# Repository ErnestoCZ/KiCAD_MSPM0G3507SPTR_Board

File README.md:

# MSPM0G3507 Board

Ein KiCad-Projekt: kompaktes Entwicklungsboard rund um den **TI MSPM0G3507SPTR**.

<!-- TODO: Foto oder 3D-Render des Boards einfügen -->
<!--  -->

## ✨ Features

- **MCU:** MSPM0G3507SPTR – Arm Cortex-M0+ mit bis zu 80 MHz, 128 KB Flash, 32 KB SRAM
- **Peripherie des Chips:** CAN-FD, 12-Bit-ADC, DAC, Op-Amp, UART, SPI, I²C
- TODO: Stromversorgung (z. B. USB-C, 3,3-V-Regler)
- TODO: Programmierung/Debugging (z. B. SWD-Header)
- TODO: Herausgeführte Pins, LEDs, Taster, Sensoren

## 📁 Projektstruktur

```text
.
├── *.kicad_pro      # KiCad-Projekt
├── *.kicad_sch      # Schaltplan
├── *.kicad_pcb      # Platinenlayout
├── libs/            # Symbole & Footprints (falls vorhanden)
└── README.md
```

## 🚀 Loslegen

1. Repository klonen:
   ```bash
   git clone https://github.com/ErnestoCZ/KiCAD_MSPM0G3507SPTR_Board.git
   ```
2. Projektdatei `*.kicad_pro` in [KiCad](https://www.kicad.org/) öffnen (TODO: Version angeben, z. B. 8.x).
3. Schaltplan und Layout ansehen, bei Bedarf Gerber-Dateien exportieren.

## 🔧 Firmware

Der MSPM0G3507 wird mit dem [TI MSPM0 SDK](https://www.ti.com/tool/MSPM0-SDK) und Code Composer Studio (oder einer Toolchain deiner Wahl) programmiert.

## 📌 Status

TODO: z. B. „Prototyp in Arbeit“ / „Rev. A bestellt“ / „getestet“

## 📄 Lizenz

TODO: Lizenz wählen (z. B. CERN-OHL-P für Hardware, MIT für Code)

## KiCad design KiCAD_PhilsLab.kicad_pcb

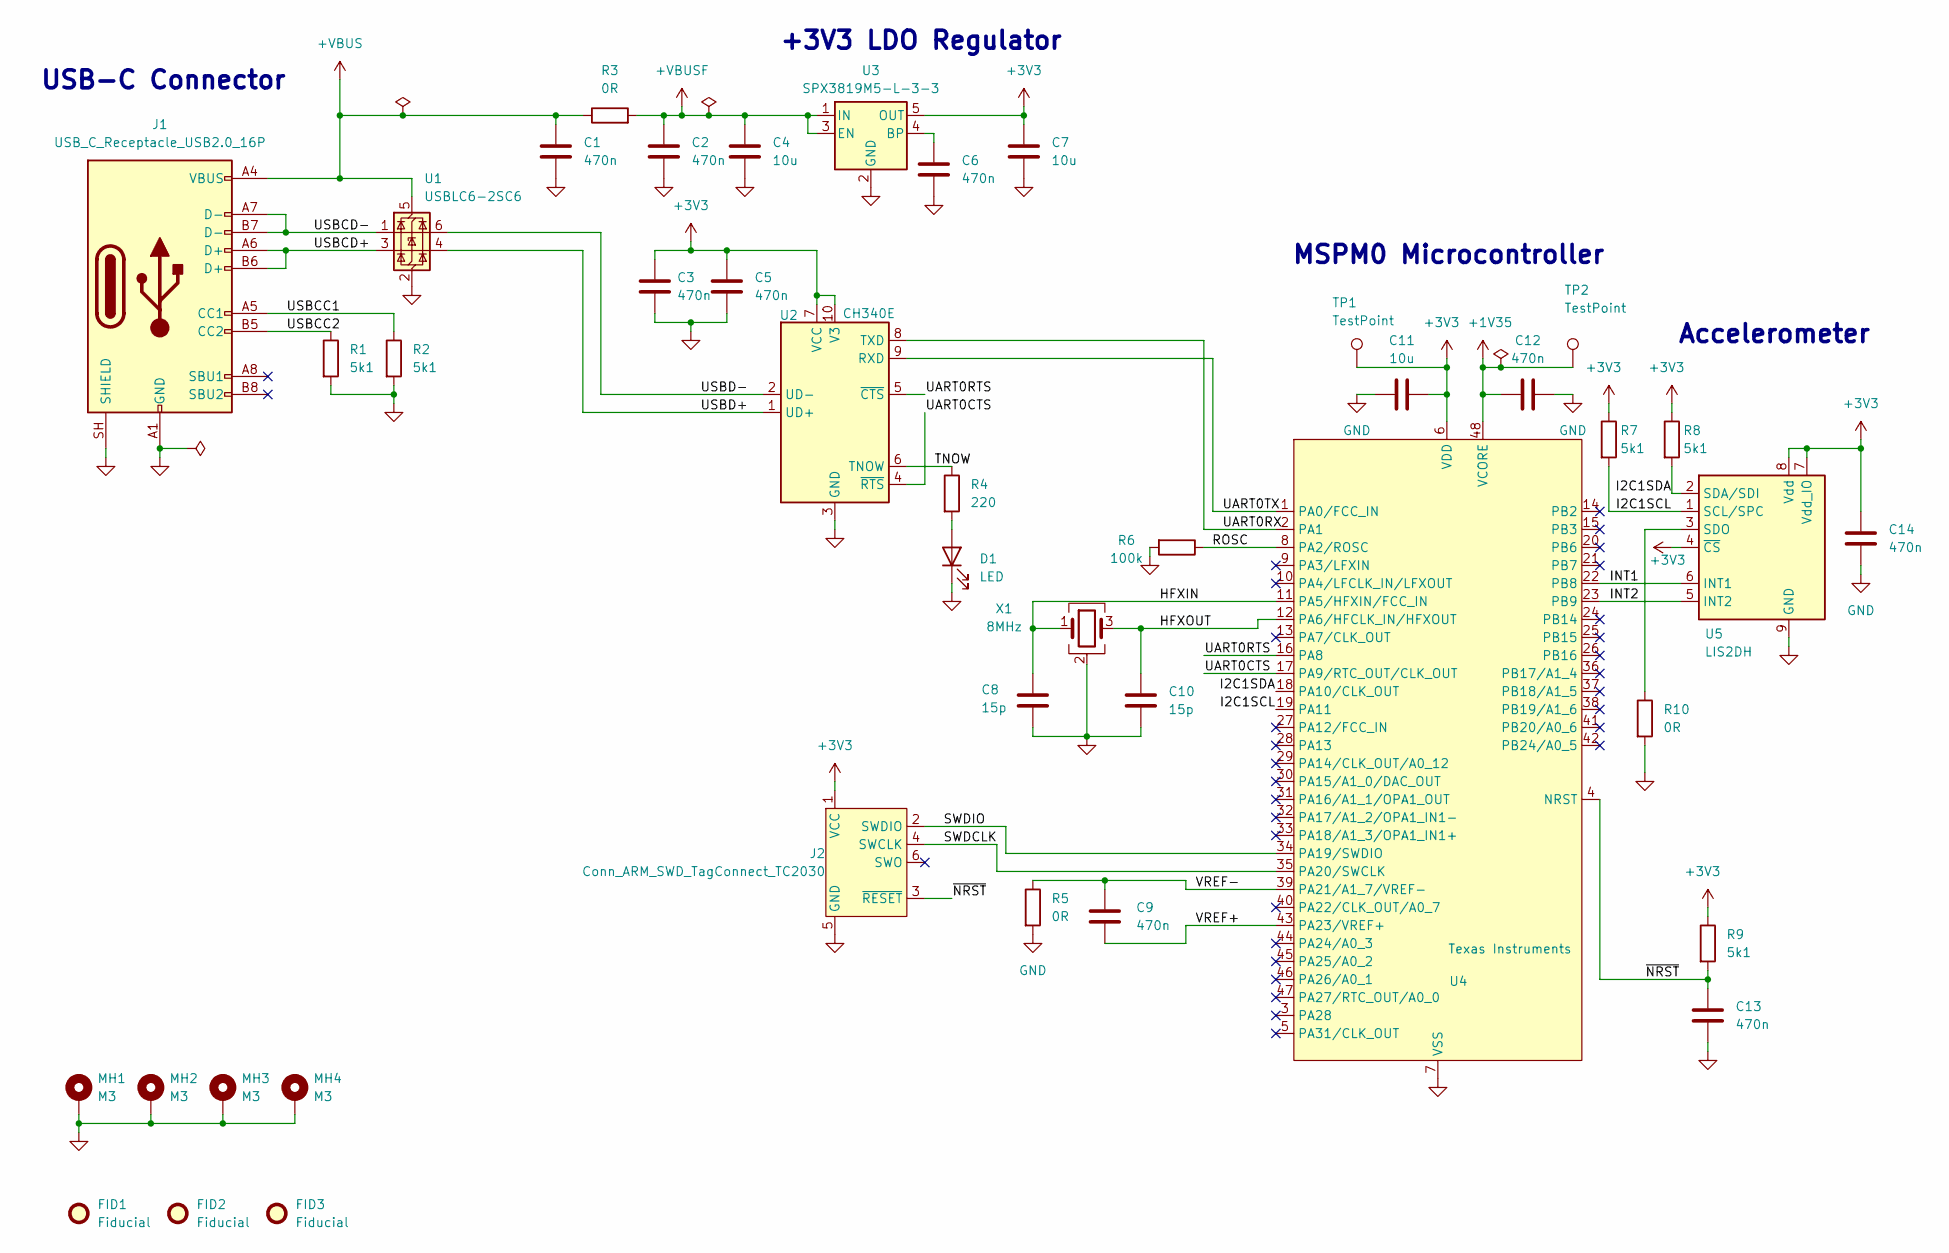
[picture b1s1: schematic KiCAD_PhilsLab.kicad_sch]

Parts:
C1, C2, C3, C5, C6, C9, C12, C13, C14: 470n; C_0603_1608Metric
C4, C7, C11: 10u; C_0805_2012Metric
C8, C10: 15p; C_0603_1608Metric
D1: LED; LED_0603_1608Metric
FID1, FID2, FID3: Fiducial; Fiducial_1mm_Mask2mm
J1: USB_C_Receptacle_USB2.0_16P; USB_C_Receptacle_GCT_USB4105-xx-A_16P_TopMnt_Horizontal
J2: Conn_ARM_SWD_TagConnect_TC2030; Tag-Connect_TC2030-IDC-FP_2x03_P1.27mm_Vertical
MH1, MH2, MH3, MH4: M3; MountingHole_3.2mm_M3_Pad_Via
R1, R2, R7, R8, R9: 5k1; R_0603_1608Metric
R3, R5, R10: 0R; R_0603_1608Metric
R4: 220; R_0201_0603Metric
R6: 100k; R_0603_1608Metric
TP1, TP2: TestPoint; TestPoint_Pad_D1.0mm
U1: USBLC6-2SC6; SOT-23-6
U2: CH340E; MSOP-10_3x3mm_P0.5mm
U3: SPX3819M5-L-3-3; SOT-23-5
U4: LQFP-48_7x7mm_P0.5mm
U5: LIS2DH; LGA-14_2x2mm_P0.35mm_LayoutBorder3x4y
X1: 8MHz; Crystal_SMD_3225-4Pin_3.2x2.5mm_HandSoldering

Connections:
+1V35: C12.1, TP2.1 (1_1), U4.48 (VCORE)
+3V3: C3.2, C5.2, C7.2, C11.2, C14.2, J2.1 (VCC), R7.1, R8.1, R9.1, TP1.1 (1_1), U2.7 (VCC), U2.10 (V3), U3.5 (OUT), U4.6 (VDD), U5.4 (~CS), U5.7 (Vdd_IO), U5.8 (Vdd)
+VBUS: C1.2, J1.A4 (VBUS), J1.A9 (VBUS), J1.B4 (VBUS), J1.B9 (VBUS), R3.1, U1.5 (VBUS)
+VBUSF: C2.2, C4.2, R3.2, U3.1 (IN), U3.3 (EN)
/HFXIN: C8.2, U4.11 (PA5/HFXIN/FCC_IN), X1.1
/HFXOUT: C10.1, U4.12 (PA6/HFCLK_IN/HFXOUT), X1.3
/I2C1SCL: R7.2, U4.19 (PA11), U5.1 (SCL/SPC)
/I2C1SDA: R8.2, U4.18 (PA10/CLK_OUT), U5.2 (SDA/SDI)
/INT1: U4.22 (PB8), U5.6 (INT1)
/INT2: U4.23 (PB9), U5.5 (INT2)
/ROSC: R6.1, U4.8 (PA2/ROSC)
/SWDCLK: J2.4 (SWCLK), U4.35 (PA20/SWCLK)
/SWDIO: J2.2 (SWDIO), U4.34 (PA19/SWDIO)
/TNOW: R4.1, U2.6 (TNOW)
/UART0CTS: U2.4 (~RTS), U4.17 (PA9/RTC_OUT/CLK_OUT)
/UART0RTS: U2.5 (~CTS), U4.16 (PA8)
/UART0RX: U2.8 (TXD), U4.2 (PA1)
/UART0TX: U2.9 (RXD), U4.1 (PA0/FCC_IN)
/USBCC1: J1.A5 (CC1), R2.1
/USBCC2: J1.B5 (CC2), R1.1
/USBCD+: J1.A6 (D+), J1.B6 (D+), U1.3 (I/O2)
/USBCD-: J1.A7 (D-), J1.B7 (D-), U1.1 (I/O1)
/USBD+: U1.4 (I/O2), U2.1 (UD+)
/USBD-: U1.6 (I/O1), U2.2 (UD-)
/VREF+: C9.2, U4.43 (PA23/VREF+)
/VREF-: C9.1, R5.1, U4.39 (PA21/A1_7/VREF-)
/~NRST: C13.1, J2.3 (~RESET), R9.2, U4.4 (NRST)
GND: C1.1, C2.1, C3.1, C4.1, C5.1, C6.1, C7.1, C8.1, C10.2, C11.1, C12.2, C13.2, C14.1, D1.1 (K), J1.A1 (GND), J1.A12 (GND), J1.B1 (GND), J1.B12 (GND), J1.SH (SHIELD), J2.5 (GND), MH1.1 (1_1), MH2.1 (1_1), MH3.1 (1_1), MH4.1 (1_1), R1.2, R2.2, R5.2, R6.2, R10.2, U1.2 (GND), U2.3 (GND), U3.2 (GND), U4.7 (VSS), U5.9 (GND), U5.11 (GND), X1.2 (G), X1.4 (G)
unnamed: D1.2 (A), R4.2
unnamed: C6.2, U3.4 (BP)
unnamed: R10.1, U5.3 (SDO)

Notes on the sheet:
MSPM0 Microcontroller
+3V3 LDO Regulator
Accelerometer
USB-C Connector

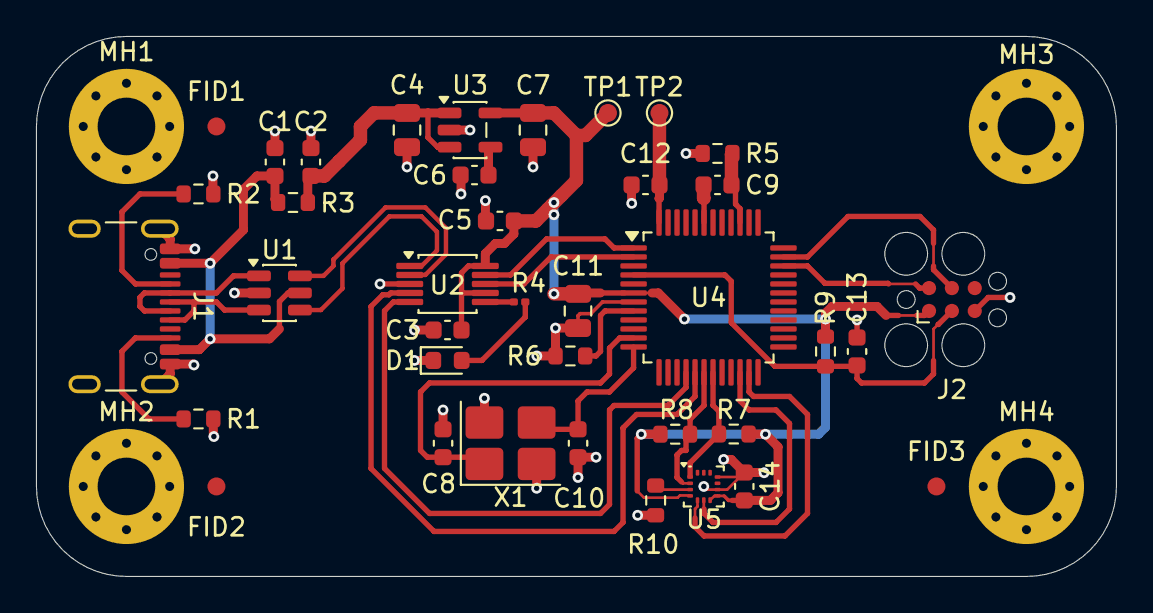
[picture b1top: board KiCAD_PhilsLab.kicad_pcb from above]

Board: 2 copper layers, 60.0 x 30.0 mm, 42 parts (0 on the bottom side), 31 nets.
